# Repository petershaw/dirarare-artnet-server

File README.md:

dirarare-artnet-server
======================

A ArtNet to DMX node

## Hardware ##
### Schematics ###

[Full sized schematics](./hardware/schematics.png).

### Partlist ###

| Part             |          Value |
|:-----------------|---------------:|
| C1               | 22p            |  
| C2               | 22p            |
| C3               | 10µ            |
| C4               | 100n           |
| C5               | 10µ            |
| C6               | 10µ            |
| C7               | 100n           |
| C11              | 220µF          |
| C14              | 100n           |
| C15              | 100n           |
| C16              | 100n           |
| C17              | 22p            |
| C18              | 22p            |
| C19              | 1n             |
| C20              | 1n             |     
| C22              | 10n            |     
| C23              | 10n            |      
| C24              | 100n           |       
| C25              | 100n           |       
| C26              | 100n           |       
| C27              | 100n           |       
| D1               | 1N4004         |         
| D3               | 1N4004         |       
| DEBUG            | TSW-101-02-S-Q |
| F1               |                |    
| FERITE           |                |           
| IC1              | MEGA328-P      |
| IC2              | 78S05          |
| IC3              | 74LS165N       |  
| IC4              | 75176AP        |
| IC5              | ENC28J60-DIL   |   
| IC6              | LM2937         |
| J1               | DCJ0202        |
| JP1              |                |
| JP2              |                |
| LED1             |                |
| LED2             |                |
| LED3             |                |
| LED4             |                | 
| Q1               | 20Mhz          |   
| Q2               | 25Mhz          | 
| R1               | 10k            |
| R2               | 820            |
| R3               | 180            |
| R4               | 180            |
| R5               | 10k            |
| R6               | 180            |
| R7               | 180            |
| R8               | 2,7k           |
| R9               | 47             |
| R10              | 47             |
| R11              | 47             |
| R12              | 47             |
| R13              | 180            |
| R14              |                |
| R15              | 180            | 
| R16              | 10k            |
| R17              | 10k            |
| R18              | 10k            |
| R19              | 10k            |
| R20              | 10k            |
| R21              | 10k            |
| R22              | 10k            |
| R23              | 10k            |
| SV1              |                |
| TR               |                |
| U$1              |                |
| X1               | 2516-5         | 

## Software ##

t.b.d. take a look in the code

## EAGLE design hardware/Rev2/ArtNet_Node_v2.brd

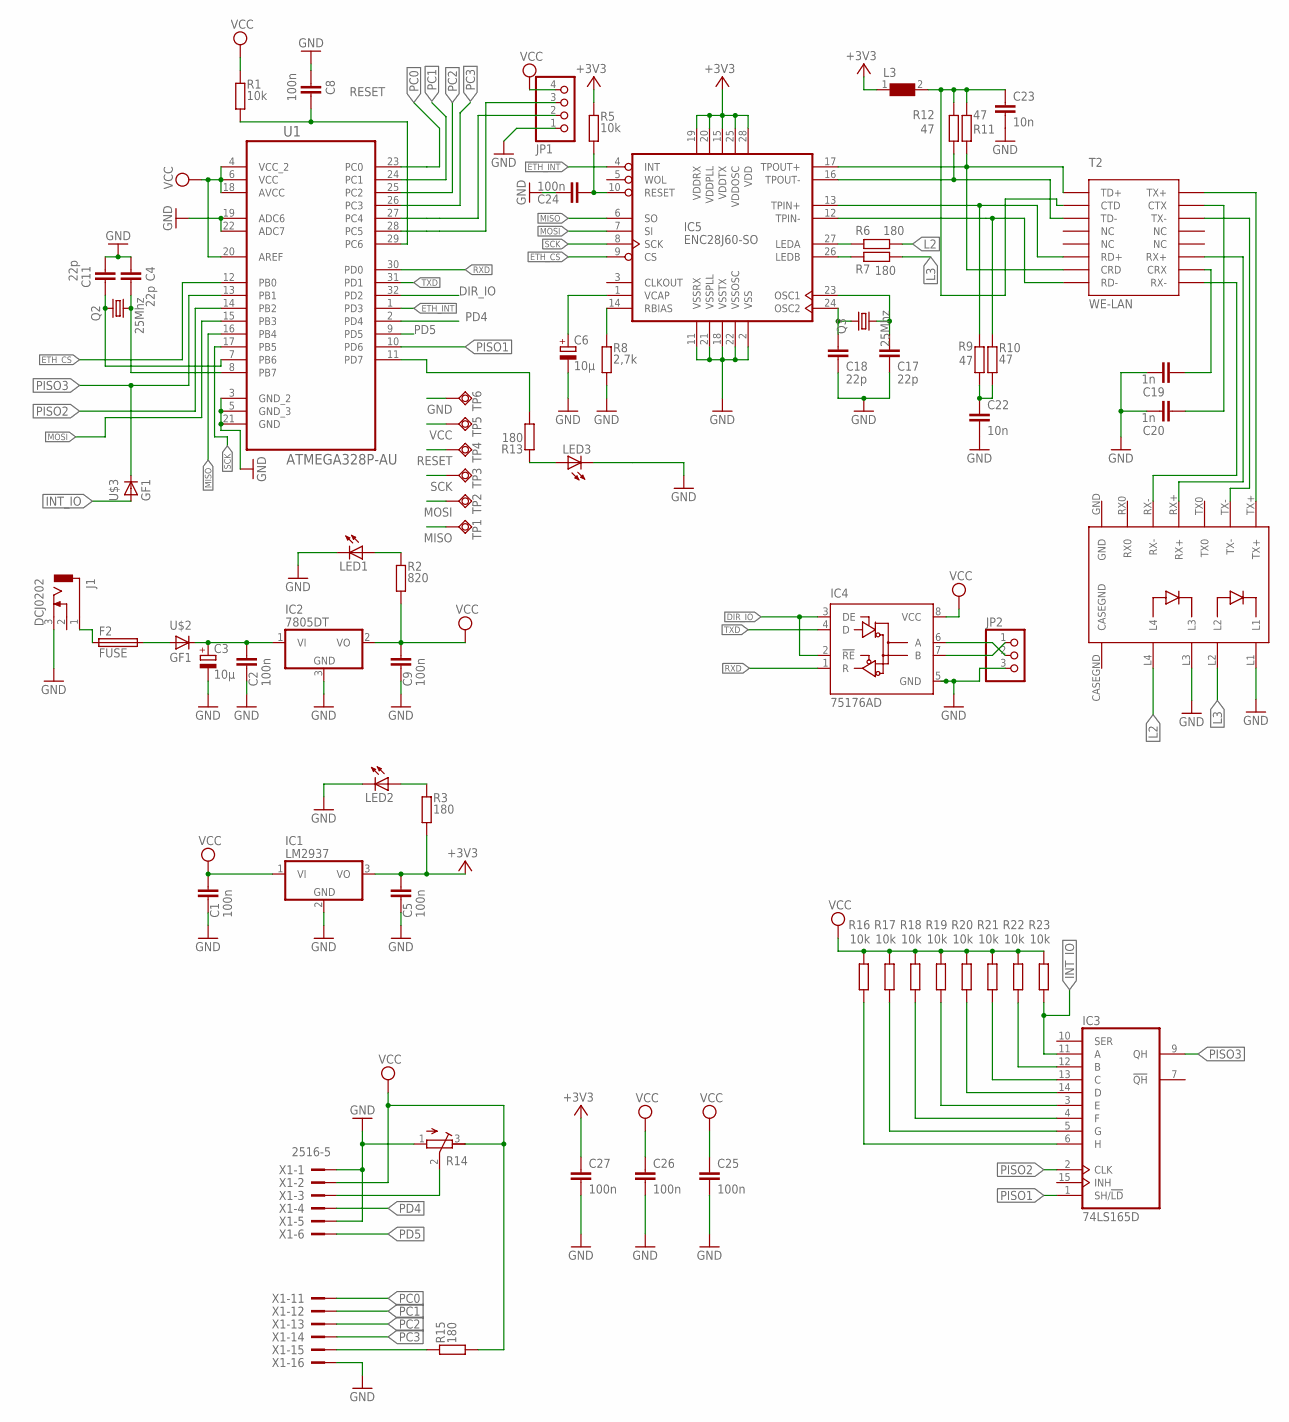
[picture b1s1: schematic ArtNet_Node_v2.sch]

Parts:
C1, C2, C5, C8, C9, C24, C25, C26, C27: 100n; C1206
C3, C6: 10µ; UD-5X5,8_NICHICON
C4, C11, C17, C18: 22p; C1206
C19, C20: 1n; C1206
C22, C23: 10n; C1206
F2: FUSE; OMNIBLOK
IC1: LM2937; TO263-3
IC2: 7805DT; TO252
IC3: 74LS165D; SO16
IC4: 75176AD; D_R-PDSO-G8
IC5: ENC28J60-SO; SO28W
J1: DCJ0202
JP1: PINHD-1X4; 1X04
JP2: PINHD-1X3; 1X03
L3: WE-SMD_7427930
LED1, LED2: LEDSML1206; SML1206
LED3: LEDSMT1206; 1206
Q2, Q3: 25Mhz; MM20SS
R1, R5, R16, R17, R18, R19, R20, R21, R22, R23: 10k; M1206
R2: 820; M1206
R3, R6, R7, R13, R15: 180; M1206
R8: 2,7k; M1206
R9, R10, R11, R12: 47; M1206
R14: R-TRIMMTS63X; RTRIMTS63X
T2: WE-LAN; WE-LAN_10/100_BASETX_7490100111
TP1, TP2, TP3, TP4, TP5, TP6: TPSQTP20SQ; TP20SQ
U1: ATMEGA328P-AU; QFP80P900X900X120-32N
U$1: 1XRJ45_MM_JACK
U$2, U$3: GF1; SMA-DO214AC
X1: 2516-5; PAK100/2500-5-16

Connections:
+3V3: C5.2, C27.1, IC1.3 (VO), IC5.15 (VDDTX), IC5.19 (VDDRX), IC5.20 (VDDPLL), IC5.25 (VDDOSC), IC5.28 (VDD), L3.1, R3.1, R5.2
DIR_IO: IC4.2 (!RE), IC4.3 (DE), U1.32 (PD2)
ETH_CS: IC5.9 (CS), U1.12 (PB0)
ETH_INT: IC5.4 (INT), U1.1 (PD3)
INT_IO: IC3.11 (A), R23.2, U$3.A
L2: R6.1, U$1.L4
L3: R7.1, U$1.L2
MISO: IC5.6 (SO), TP1.TP, U1.16 (PB4)
MOSI: IC5.7 (SI), TP2.TP, U1.15 (PB3)
unnamed: T2.16 (TX+), U$1.TX+
unnamed: C19.1, T2.10 (CRX)
unnamed: T2.14 (TX-), U$1.TX-
unnamed: C20.1, T2.15 (CTX)
unnamed: F2.P$2 (2), U$2.A
unnamed: T2.11 (RX+), U$1.RX+
unnamed: T2.9 (RX-), U$1.RX-
unnamed: IC4.7 (B), JP2.1
unnamed: F2.P$1 (1), J1.1
unnamed: IC5.27 (LEDA), R6.2
unnamed: JP1.2, U1.27 (PC4)
unnamed: IC4.6 (A), JP2.2
unnamed: IC5.26 (LEDB), R7.2
unnamed: C2.2, C3.+, IC2.1 (VI), U$2.K (C)
unnamed: LED2.A, R3.2
unnamed: C18.2, IC5.24 (OSC2), Q3.4 (2)
unnamed: C17.2, IC5.23 (OSC1), Q3.1
unnamed: IC5.12 (TPIN-), R10.2, T2.8 (RD-)
unnamed: IC5.13 (TPIN+), R9.2, T2.6 (RD+)
unnamed: IC5.16 (TPOUT-), R12.2, T2.3 (TD-)
unnamed: IC5.17 (TPOUT+), R11.2, T2.1 (TD+), T2.7 (CRD)
unnamed: IC5.14 (RBIAS), R8.2
unnamed: C6.+, IC5.1 (VCAP)
unnamed: JP1.3, U1.28 (PC5)
unnamed: C22.1, R9.1, R10.1
unnamed: C24.2, IC5.10 (RESET), R5.1
unnamed: LED1.A, R2.2
unnamed: R13.1, U1.11 (PD7)
unnamed: R14.2 (S), X1.3
unnamed: LED3.A, R13.2
unnamed: R15.2, X1.15
unnamed: IC3.12 (B), R22.2
unnamed: IC3.13 (C), R21.2
unnamed: IC3.14 (D), R20.2
unnamed: IC3.3 (E), R19.2
unnamed: IC3.4 (F), R18.2
unnamed: IC3.5 (G), R17.2
unnamed: IC3.6 (H), R16.2
unnamed: C4.1, Q2.1, U1.8 (PB7)
unnamed: C11.1, Q2.4 (2), U1.7 (PB6)
unnamed: C23.1, L3.2, R11.1, R12.1, T2.2 (CTD)
PC0: U1.23 (PC0), X1.11
PC1: U1.24 (PC1), X1.12
PC2: U1.25 (PC2), X1.13
PC3: U1.26 (PC3), X1.14
PD4: U1.2 (PD4), X1.4
PD5: U1.9 (PD5), X1.6
PISO1: IC3.1 (SH/!LD), U1.10 (PD6)
PISO2: IC3.2 (CLK), U1.14 (PB2)
PISO3: IC3.9 (QH), U1.13 (PB1), U$3.K (C)
RESET: C8.1, R1.1, TP4.TP, U1.29 (PC6)
RXD: IC4.1 (R), U1.30 (PD0)
TXD: IC4.4 (D), U1.31 (PD1)
VCC: C1.2, C9.2, C25.2, C26.1, IC1.1 (VI), IC2.2 (VO), IC3.16 (VCC), IC4.8 (VCC), JP1.4, R1.2, R2.1, R14.3 (A), R15.1, R16.1, R17.1, R18.1, R19.1, R20.1, R21.1, R22.1, R23.1, TP5.TP, U1.4 (VCC_2), U1.6 (VCC), U1.18 (AVCC), U1.20 (AREF), X1.2

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
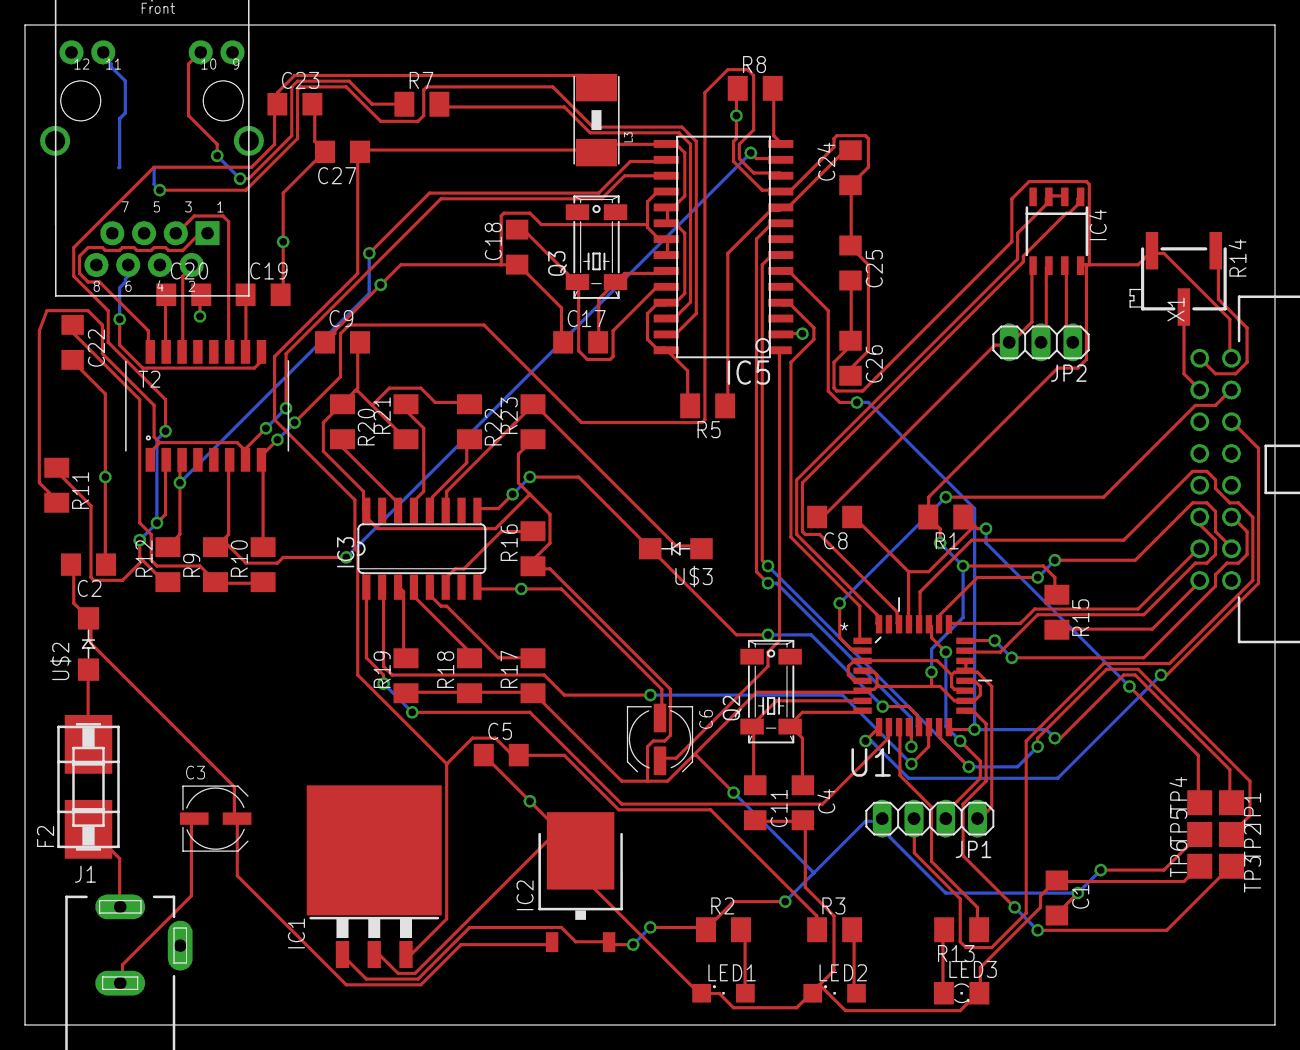
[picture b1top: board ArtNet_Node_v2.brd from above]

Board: 2 copper layers, 100.0 x 80.0 mm, 68 parts (1 on the bottom side), 64 nets.

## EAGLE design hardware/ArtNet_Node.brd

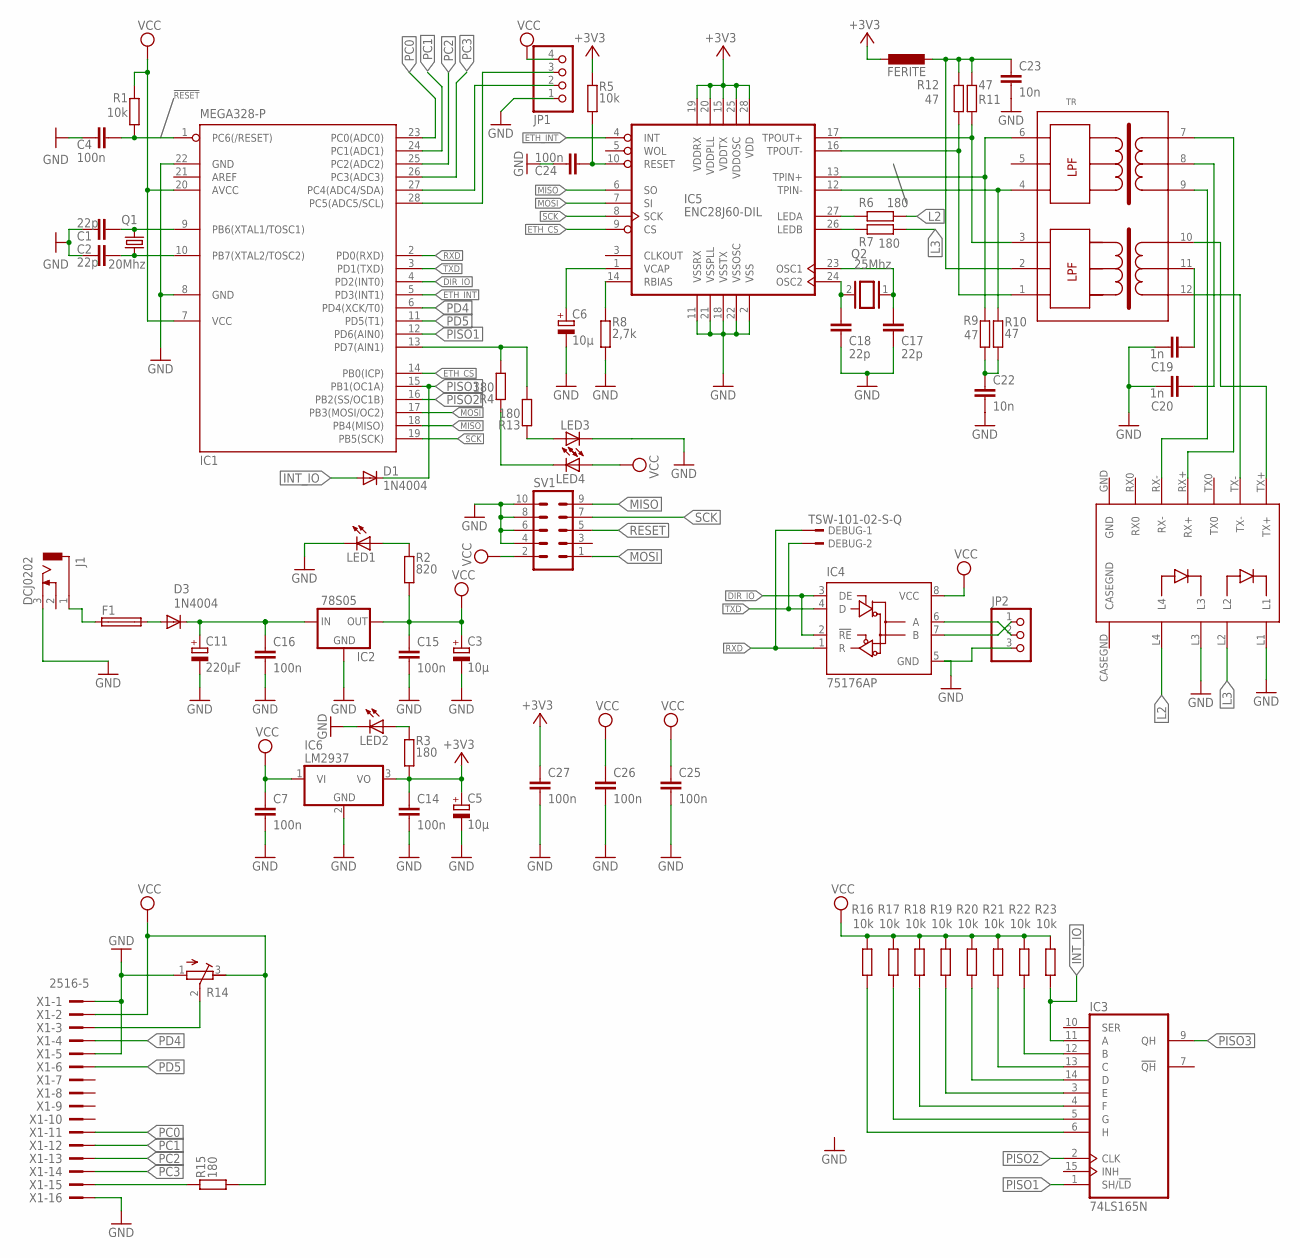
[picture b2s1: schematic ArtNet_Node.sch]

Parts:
C1, C2, C17, C18: 22p; C025-024X044
C3, C5, C6: 10µ; E2-5
C4, C7, C14, C24: 100n; C025-024X044
C11: 220µF; E3,5-8
C15, C16: 100n; C050-024X044
C19, C20: 1n; C025-024X044
C22, C23: 10n; C025-025X050
C25, C26, C27: 100n; C025-025X050
D1, D3: 1N4004; DO41-10
DEBUG: TSW-101-02-S-Q
F1: PICOFUSE
FERITE: L-EU0204/5; 0204/5
IC1: MEGA328-P; DIL28-3
IC2: 78S05; 78XXL
IC3: 74LS165N; DIL16
IC4: 75176AP; DIL08
IC5: ENC28J60-DIL; DIL28-3
IC6: LM2937; TO263-3
J1: DCJ0202
JP1: PINHD-1X4; 1X04
JP2: PINHD-1X3; 1X03
LED1, LED2, LED3, LED4: LED5MM
Q1: 20Mhz; HC49U-V
Q2: 25Mhz; QS
R1, R5, R16, R17, R18, R19, R20, R21, R22, R23: 10k; 0207/10
R2: 820; 0207/10
R3, R4, R6, R7, R13, R15: 180; 0207/10
R8: 2,7k; 0207/10
R9, R10, R11, R12: 47; 0207/10
R14: R-TRIMM74X; RTRIM74X
SV1: ML10L
TR: 20F001; DIL16/12
U$1: 1XRJ45_MM_JACK
X1: 2516-5; PAK100/2500-5-16

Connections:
!RESET: C4.2, IC1.1 (PC6(/RESET)), R1.1
+3V3: C5.+, C14.1, C27.1, FERITE.1, IC5.15 (VDDTX), IC5.19 (VDDRX), IC5.20 (VDDPLL), IC5.25 (VDDOSC), IC5.28 (VDD), IC6.3 (VO), R3.1, R5.2
DIR_IO: IC1.4 (PD2(INT0)), IC4.2 (!RE), IC4.3 (DE)
ETH_CS: IC1.14 (PB0(ICP)), IC5.9 (CS)
ETH_INT: IC1.5 (PD3(INT1)), IC5.4 (INT)
GND: C1.1, C2.1, C3.-, C4.1, C5.-, C6.-, C7.2, C11.-, C14.2, C15.2, C16.2, C17.1, C18.1, C19.2, C20.2, C22.2, C23.2, C24.1, C25.1, C26.2, C27.2, IC1.8 (GND), IC1.22 (GND), IC2.GND, IC3.8 (GND), IC4.5 (GND), IC5.2 (VSS), IC5.11 (VSSRX), IC5.18 (VSSTX), IC5.21 (VSSPLL), IC5.22 (VSSOSC), IC6.2 (GND), J1.3, JP1.1, JP2.3, LED1.K (C), LED2.K (C), LED3.K (C), R8.1, R14.1 (E), SV1.4, SV1.6, SV1.8, SV1.10, U$1.L1, U$1.L3, X1.1, X1.5, X1.16
L2: R6.1, U$1.L4
L3: R7.1, U$1.L2
MISO: IC1.18 (PB4(MISO)), IC5.6 (SO), SV1.9
MOSI: IC1.17 (PB3(MOSI/OC2)), IC5.7 (SI), SV1.1
unnamed: C2.2, IC1.10 (PB7(XTAL2/TOSC2)), Q1.1
unnamed: C1.2, IC1.9 (PB6(XTAL1/TOSC1)), Q1.2
unnamed: TR.9, U$1.RX-
unnamed: D3.A, F1.2
unnamed: TR.12, U$1.TX-
unnamed: TR.10, U$1.TX+
unnamed: IC4.7 (B), JP2.1
unnamed: F1.1, J1.1
unnamed: IC5.27 (LEDA), R6.2
unnamed: IC1.27 (PC4(ADC4/SDA)), JP1.2
unnamed: IC4.6 (A), JP2.2
unnamed: IC5.26 (LEDB), R7.2
unnamed: TR.7, U$1.RX+
unnamed: C20.1, TR.8
unnamed: C19.1, TR.11
unnamed: C18.2, IC5.24 (OSC2), Q2.2
unnamed: C17.2, IC5.23 (OSC1), Q2.1
unnamed: IC5.12 (TPIN-), R10.2, TR.4
unnamed: IC5.13 (TPIN+), R9.2, TR.6
unnamed: IC5.16 (TPOUT-), R12.2, TR.1
unnamed: IC5.17 (TPOUT+), R11.2, TR.3
unnamed: IC5.14 (RBIAS), R8.2
unnamed: C6.+, IC5.1 (VCAP)
unnamed: IC1.28 (PC5(ADC5/SCL)), JP1.3
unnamed: C22.1, R9.1, R10.1
unnamed: C24.2, IC5.10 (RESET), R5.1
unnamed: LED1.A, R2.2
unnamed: LED2.A, R3.2
unnamed: IC1.13 (PD7(AIN1)), R4.1, R13.1
unnamed: R14.2 (S), X1.3
unnamed: LED3.A, R13.2
unnamed: LED4.K (C), R4.2
unnamed: D1.A, IC3.11 (A), R23.2
unnamed: R15.2, X1.15
unnamed: IC3.12 (B), R22.2
unnamed: IC3.13 (C), R21.2
unnamed: IC3.14 (D), R20.2
unnamed: IC3.3 (E), R19.2
unnamed: IC3.4 (F), R18.2
unnamed: IC3.5 (G), R17.2
unnamed: IC3.6 (H), R16.2
unnamed: C23.1, FERITE.2, R11.1, R12.1, TR.2
unnamed: C11.+, C16.1, D3.C, IC2.IN
PC0: IC1.23 (PC0(ADC0)), X1.11
PC1: IC1.24 (PC1(ADC1)), X1.12
PC2: IC1.25 (PC2(ADC2)), X1.13
PC3: IC1.26 (PC3(ADC3)), X1.14
PD4: IC1.6 (PD4(XCK/T0)), X1.4
PD5: IC1.11 (PD5(T1)), X1.6
PISO1: IC1.12 (PD6(AIN0)), IC3.1 (SH/!LD)
PISO2: IC1.16 (PB2(SS/OC1B)), IC3.2 (CLK)
PISO3: D1.C, IC1.15 (PB1(OC1A)), IC3.9 (QH)
RESET: SV1.5
RXD: DEBUG.1, IC1.2 (PD0(RXD)), IC4.1 (R)
SCK: IC1.19 (PB5(SCK)), IC5.8 (SCK), SV1.7
TXD: DEBUG.2, IC1.3 (PD1(TXD)), IC4.4 (D)
VCC: C3.+, C7.1, C15.1, C25.2, C26.1, IC1.7 (VCC), IC1.20 (AVCC), IC2.OUT, IC3.16 (VCC), IC4.8 (VCC), IC6.1 (VI), JP1.4, R1.2, R2.1, R14.3 (A), R15.1, R16.1, R17.1, R18.1, R19.1, R20.1, R21.1, R22.1, R23.1, SV1.2, X1.2

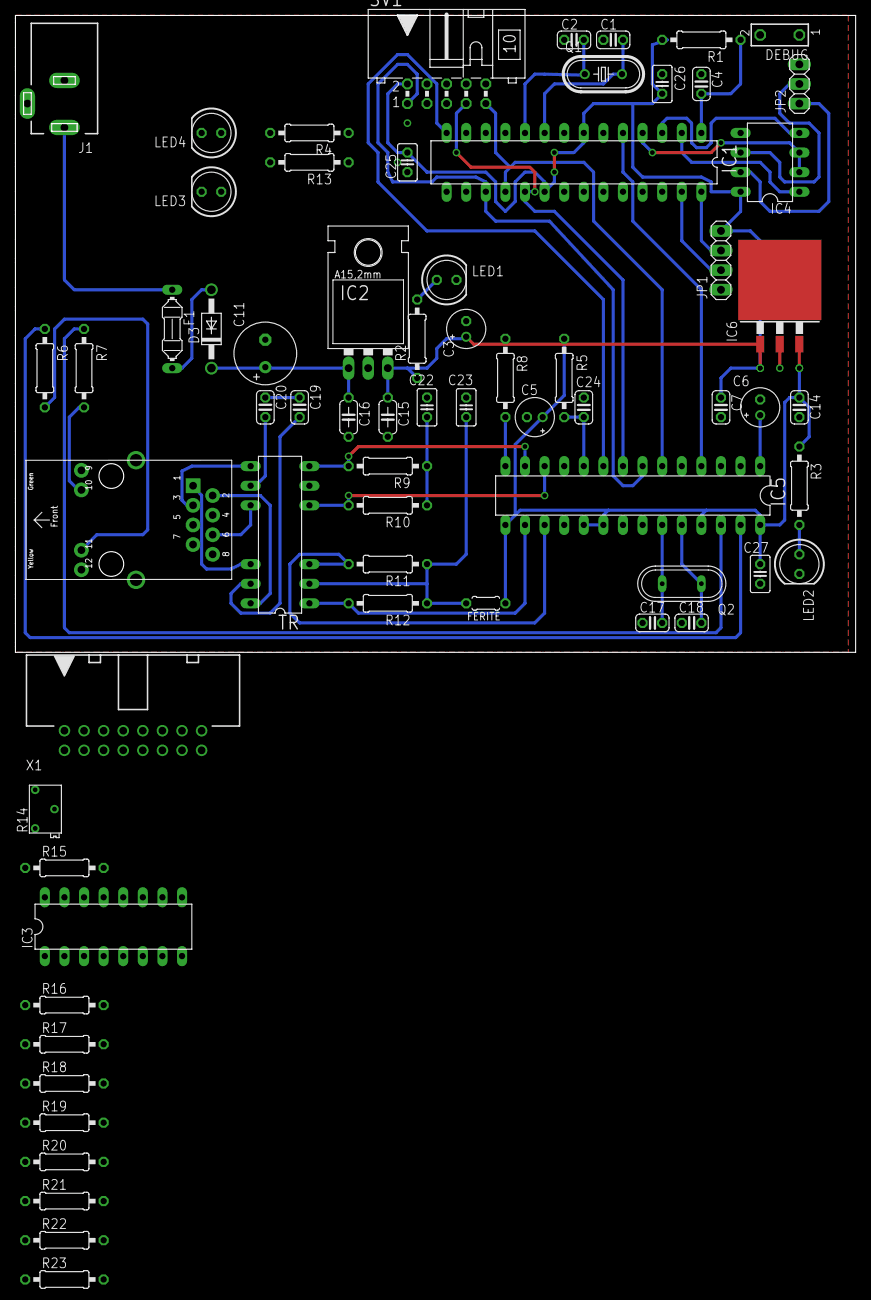
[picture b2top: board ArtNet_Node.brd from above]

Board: 2 copper layers, 108.9 x 82.5 mm, 67 parts (0 on the bottom side), 66 nets.

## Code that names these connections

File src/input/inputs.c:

#include "inputs.h"
#include "../global.h"
#include "../config.h"
#include <avr/io.h>
#include <avr/interrupt.h>


//volatile uint8_t portbhistory = 0xFF;

void initialize_inputs(void){
	next_action = 0;
	
	//ROTARY ENCODER SETUP
	//------------------------------------------------------------------
	
	// PB0,PB1,PB2 as inputs
	ENCODER_REGISTER &= ~(1 << ENCODER_PIN_TURN0) |
						~(1 << ENCODER_PIN_TURN1);
    
    /*//Enable pull-up
    ENCODER_PORT |= (1 << ENCODER_PIN_PUSH) |
					(1 << ENCODER_PIN_TURN0) |
					(1 << ENCODER_PIN_TURN1);*/

	int8_t new;
	new = 0;
	if( PINB & 1<<PB1 )
		new = 3;
	if( PINB & 1<<PB2 )
		new ^= 1;                   // convert gray to binary
	last = new;                   // power on state
	enc_delta = 0;
	
    //Debug LED
    DDRD |= (1 << PD6);
    
	DDRB &= ~(1 << DDB0);
    PORTB |= (1 << PORTB0);
    
    PCICR |= (1 << PCIE0);    // set PCIE0 to enable PCMSK0 scan
    PCMSK0 |= (1 << PCINT0);  // set PCINT0 to trigger an interrupt on state change 

    sei();
    
}
	
	//------------------------------------------------------------------
	//END ROTARY ENCODER SETUP
	

/* INTERRUPT
   -----------------------------------------
   Inputs are not listening until should_read
   is true
   -----------------------------------------
*/
ISR (PCINT0_vect)
{
    /* interrupt code here */
    ENCODER_TIMER2_ON;
    next_action = PRESSED_ENTER;
}


int8_t encode_read1( void )         // read single step encoders
{
  int8_t val;
 
  cli();
  val = enc_delta;
  enc_delta = 0;
  sei();
  return val;                   // counts since last call
}
 

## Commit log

2014-04-17 REV.1
    Initial commit.
    _works on the test board
2014-04-17 Add schematics
2014-04-17 Add full size schematics
2014-08-07 Rev2 First Commit
2014-08-07 add ignore file
2014-08-28 set Fuses while upload
    The AVR use a 16MHZ, the fuse bit's are nessassary to set.
2014-08-28 init revision 2
2014-08-28 rewrite menucontroller button handling
2014-08-28 Boot the display first
    Frst task is to boot up the display now.
2014-08-28 cleanup input code
    while next_action is an global variable, all input state functions are removed
2014-08-29 cleanup menucode
2014-08-29 remove a warning. Syntax
2014-08-29 Remove status LED
2014-08-29 cleanup unused configuration variables
2014-08-29 set header for revision 2
2014-08-29 Fixes compiler warning for main.c
2014-08-29 Rotary Encoder Code
2014-08-30 Rotary encoder via timer
2014-09-02 Encoder Timer Debug Session
2014-09-02 Encoder Menu Code

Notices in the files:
parts and their libraries:
wuerth_elektronik_eisos__v6.5: Copyright: WÃ¼rth Elektronik
wuerth_elektronik_eisos__v6.5: Copyright: Würth Elektronik
